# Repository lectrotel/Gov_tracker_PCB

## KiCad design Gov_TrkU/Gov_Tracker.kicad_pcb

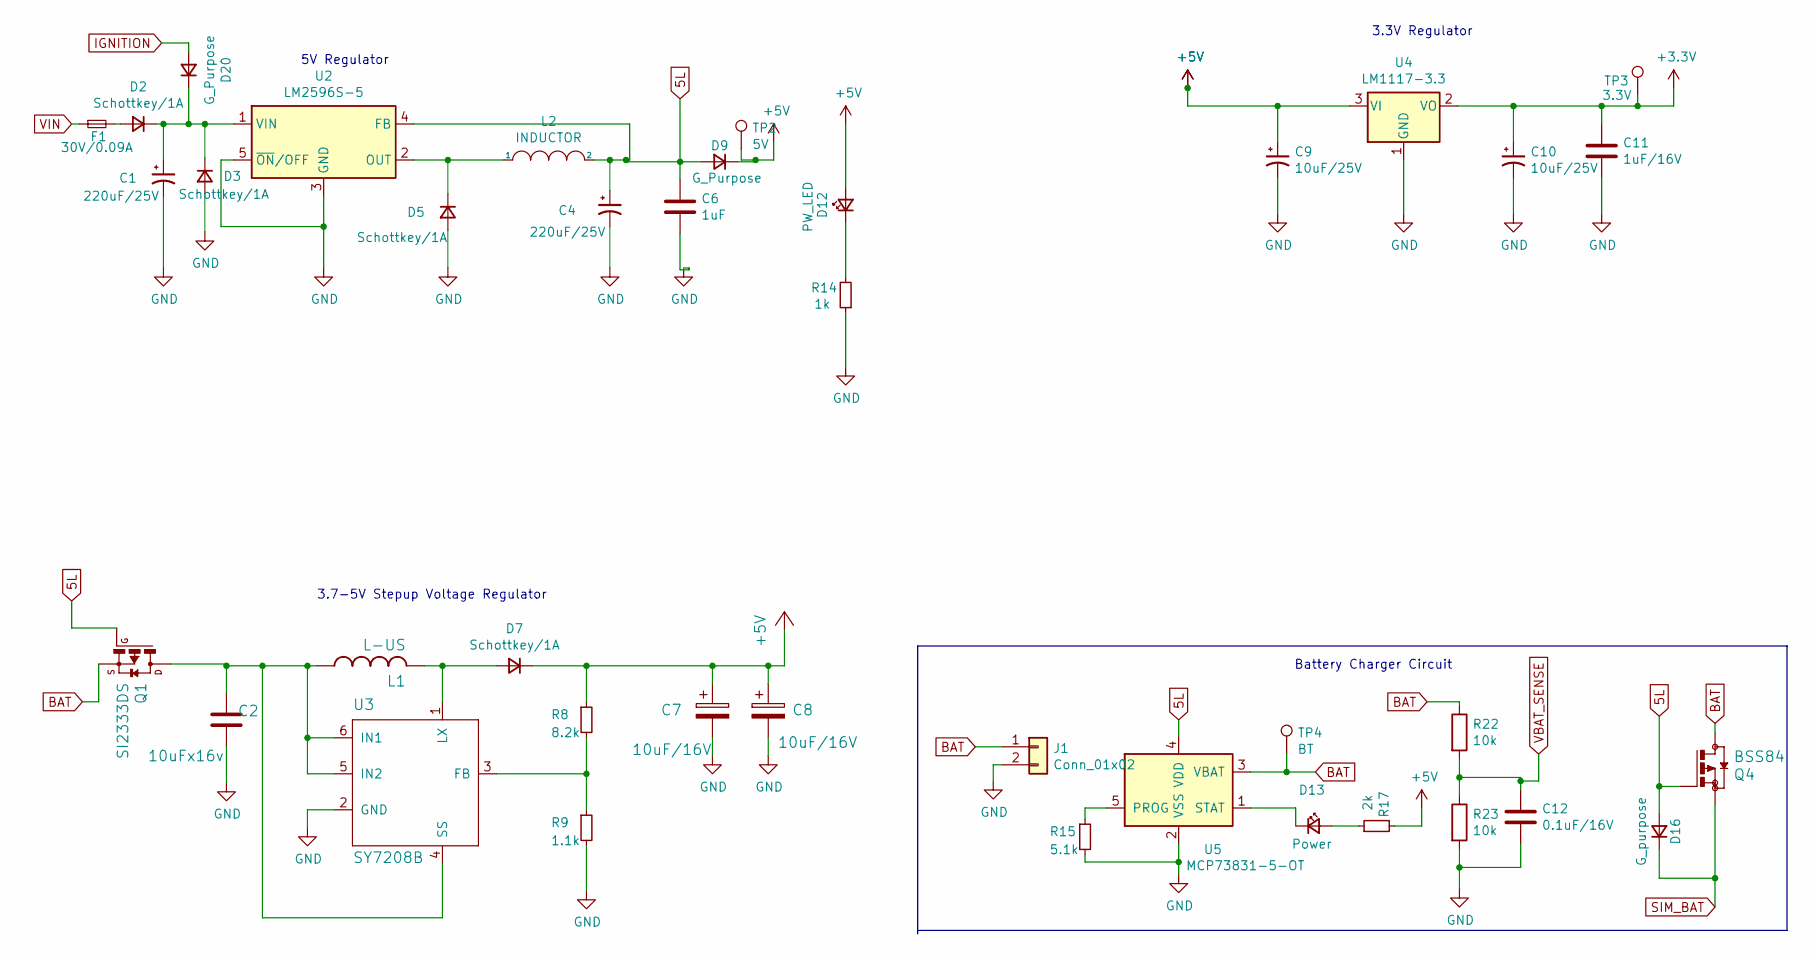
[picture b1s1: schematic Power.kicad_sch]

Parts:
C1, C4: 220uF/25V; CP_Elec_8x6.9
C2: 10uFx16v; C_0603_1608Metric
C6: 1uF; C_0603_1608Metric
C7, C8: 10uF/16V; C_0603_1608Metric
C9, C10: 10uF/25V; CP_Radial_D5.0mm_P2.50mm
C11: 1uF/16V; C_0603_1608Metric
C12: 0.1uF/16V; C_0603_1608Metric
D2, D3, D5, D7: Schottkey/1A; D_SMA
D9, D20: G_Purpose; D_SMA
D12: PW_LED; LED_0805_2012Metric
D13: Power; LED_0805_2012Metric
D16: G_purpose; D_SMA
F1: 30V/0.09A; Fuse_BelFuse_0ZRE0005FF_L8.3mm_W3.8mm
J1: Conn_01x02; JST_PH_B2B-PH-K_1x02_P2.00mm_Vertical
L1: L-US; L_Taiyo-Yuden_NR-60xx
L2: INDUCTOR; L_Pulse_PA4320
Q1: SI2333DS; SC-59
Q4: BSS84; SOT-23
R8: 8.2k; R_0603_1608Metric
R9: 1.1k; R_0603_1608Metric
R14: 1k; R_0603_1608Metric
R15: 5.1k; R_0603_1608Metric
R17: 2k; R_0603_1608Metric
R22, R23: 10k; R_0603_1608Metric
TP2: 5V; TestPoint_Pad_1.0x1.0mm
TP3: 3.3V; TestPoint_Pad_1.0x1.0mm
TP4: BT; TestPoint_Pad_1.0x1.0mm
U2: LM2596S-5; TO-263-5_TabPin3
U3: SY7208B; SOT-23-6
U4: LM1117-3.3; SOT-223-3_TabPin2
U5: MCP73831-5-OT; SOT-23-5

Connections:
5L: C4.1, C6.1, D9.2 (A), D16.2 (A), L2.2, Q1.1 (G), Q4.1 (G), U2.4 (FB), U5.4 (VDD); also elsewhere on the board
+5V: C7.1, C8.1, C9.1, D7.1 (K), D9.1 (K), D12.2 (A), R8.1, R17.2, TP2.1, U4.3 (VI); also elsewhere on the board
BAT: J1.1, Q1.2 (S), Q4.3 (D), R22.1, TP4.1, U5.3 (VBAT)
GND: C1.2, C2.2, C4.2, C6.2, C7.2, C8.2, C9.2, C10.2, C11.2, C12.2, D3.2 (A), D5.2 (A), J1.2, R9.2, R14.1, R15.2, R23.2, U2.3 (GND), U2.5 (~ON/OFF), U3.2 (GND), U4.1 (GND), U5.2 (VSS); also elsewhere on the board
IGNITION: D20.2 (A); also elsewhere on the board
unnamed: D2.2 (A), F1.2
unnamed: C1.1, D2.1 (K), D3.1 (K), D20.1 (K), U2.1 (VIN)
unnamed: D5.1 (K), L2.1, U2.2 (OUT)
unnamed: D7.2 (A), L1.2, U3.1 (LX)
unnamed: D12.1 (K), R14.2
unnamed: D13.2 (A), R17.1
unnamed: D13.1 (K), U5.1 (STAT)
unnamed: C2.1, L1.1, Q1.3 (D), U3.4 (SS), U3.5 (IN2), U3.6 (IN1)
unnamed: R8.2, R9.1, U3.3 (FB)
unnamed: R15.1, U5.5 (PROG)
SIM_BAT: D16.1 (K), Q4.2 (S); also elsewhere on the board
VBAT_SENSE: C12.1, R22.2, R23.1; also elsewhere on the board
VIN: F1.1; also elsewhere on the board

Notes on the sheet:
3.7-5V Stepup Voltage Regulator
Battery Charger Circuit
3.3V Regulator
5V Regulator

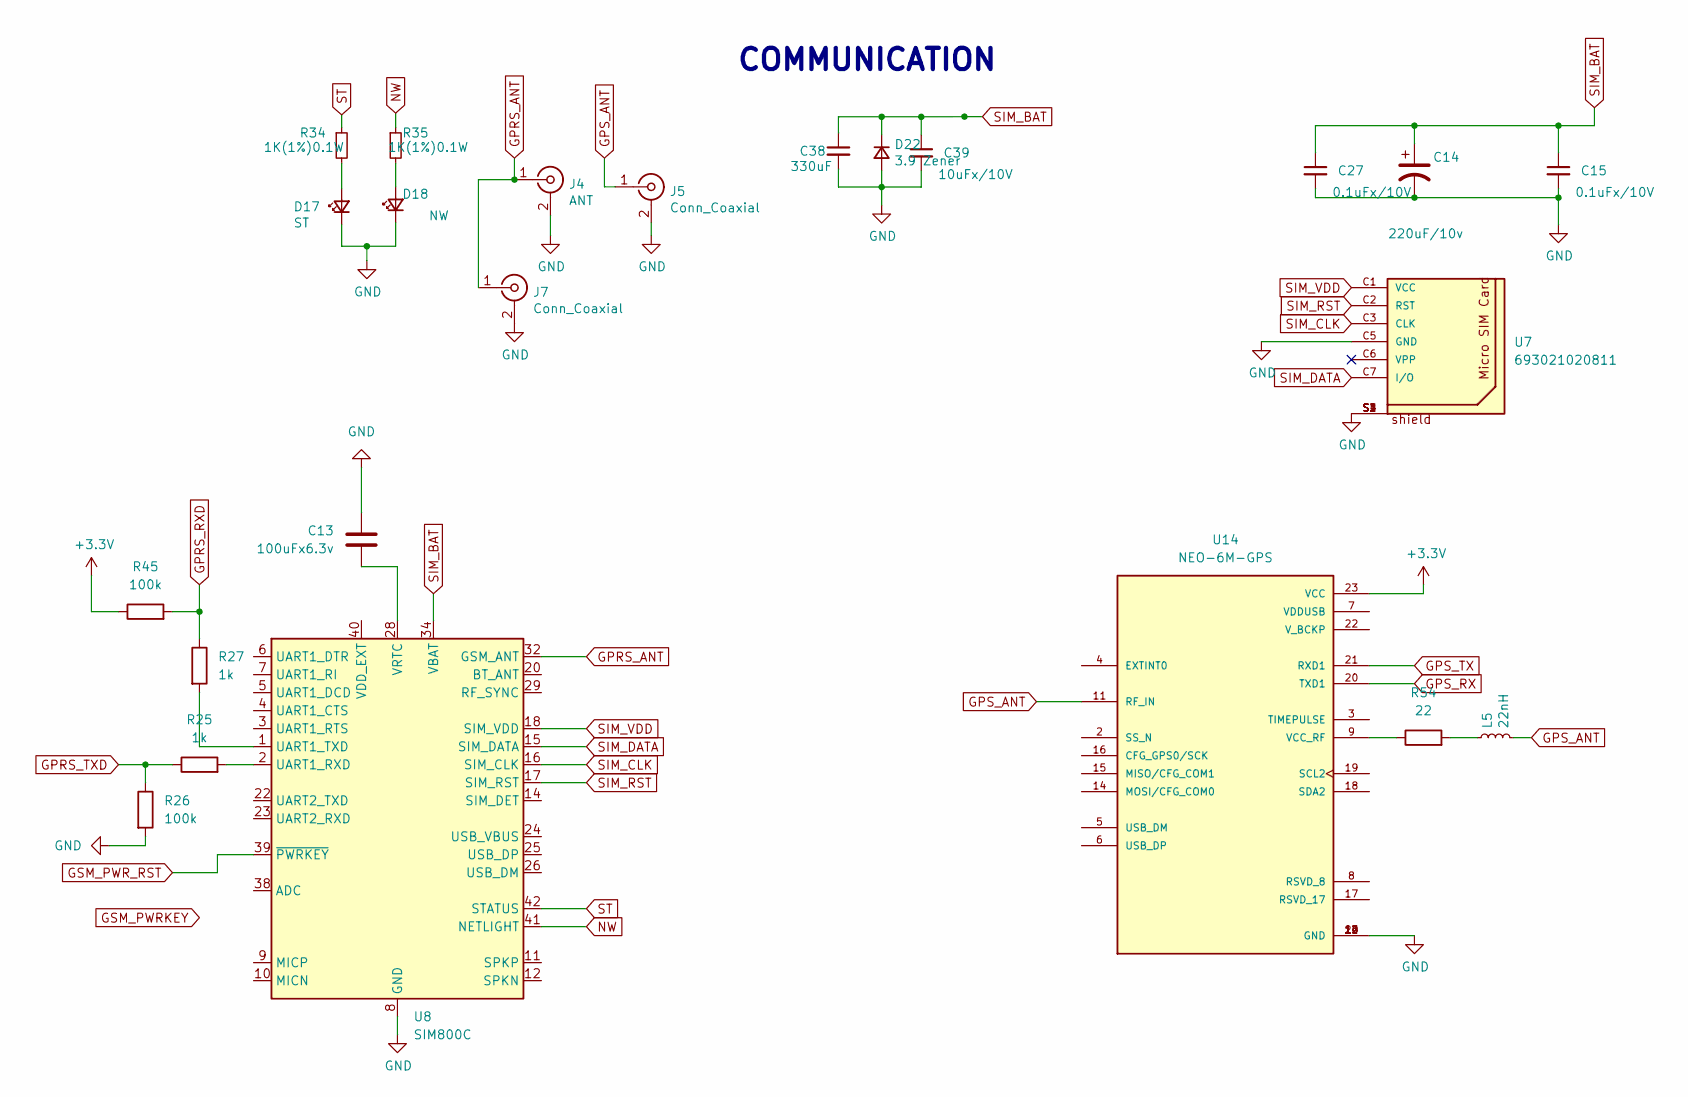
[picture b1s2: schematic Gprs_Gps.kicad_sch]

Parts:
C13: 100uFx6.3v; C_Elec_5x5.8
C14: 220uF/10v; CP_Elec_8x6.5
C15, C27: 0.1uFx/10V; C_0805_2012Metric
C38: 330uF; CP_EIA-6032-15_Kemet-U
C39: 10uFx/10V; C_0603_1608Metric
D17: ST; LED_0805_2012Metric
D18: NW; LED_0805_2012Metric
D22: 3.9 Zener; D_SOD-123
J4: ANT; SMA_Amphenol_132291_Vertical
J5: Conn_Coaxial; SMA_Amphenol_132291_Vertical
J7: Conn_Coaxial; U.FL_Molex_MCRF_73412-0110_Vertical
L5: 22nH; L_1206_3216Metric
R25, R27: 1k; R_0603_1608Metric
R26, R45: 100k; R_0603_1608Metric
R34, R35: 1K(1%)0.1W; R_0603_1608Metric
R54: 22; R_0603_1608Metric
U7: 693021020811; PART-NUMBER 693120035011
U8: SIM800C; SIMCom_SIM800C
U14: NEO-6M-GPS; XCVR_NEO-6M-GPS; PARTREV R15

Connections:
GND: C13.1, C14.2, C15.2, C27.2, C38.2, C39.2, D17.1 (K), D18.1 (K), D22.2 (A), J4.2 (Ext), J5.2 (Ext), J7.2 (Ext), R26.2, U7.C5 (GND), U7.S1, U7.S2, U7.S3, U7.S4, U8.8 (GND), U8.13 (GND), U8.19 (GND), U8.21 (GND), U8.27 (GND), U8.30 (GND), U8.31 (GND), U8.33 (GND), U8.36 (GND), U8.37 (GND), U14.10 (GND), U14.12 (GND), U14.13 (GND), U14.24 (GND); also elsewhere on the board
GPRS_ANT: J4.1 (In), J7.1 (In), U8.32 (GSM_ANT)
GPRS_RXD: R27.1, R45.2; also elsewhere on the board
GPRS_TXD: R25.1, R26.1; also elsewhere on the board
GPS_ANT: J5.1 (In), L5.2, U14.11 (RF_IN)
GPS_RX: U14.20 (TXD1); also elsewhere on the board
GPS_TX: U14.21 (RXD1); also elsewhere on the board
GSM_PWR_RST: U8.39 (~PWRKEY); also elsewhere on the board
NW: R35.1, U8.41 (NETLIGHT)
unnamed: D17.2 (A), R34.2
unnamed: D18.2 (A), R35.2
unnamed: L5.1, R54.2
unnamed: R25.2, U8.2 (UART1_RXD)
unnamed: R27.2, U8.1 (UART1_TXD)
unnamed: C13.2, U8.28 (VRTC)
unnamed: R54.1, U14.9 (VCC_RF)
SIM_BAT: C14.1, C15.1, C27.1, C38.1, C39.1, D22.1 (K), U8.34 (VBAT), U8.35 (VBAT); also elsewhere on the board
SIM_CLK: U7.C3 (CLK), U8.16 (SIM_CLK)
SIM_DATA: U7.C7 (I/O), U8.15 (SIM_DATA)
SIM_RST: U7.C2 (RST), U8.17 (SIM_RST)
SIM_VDD: U7.C1 (VCC), U8.18 (SIM_VDD)
ST: R34.1, U8.42 (STATUS)

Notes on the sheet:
COMMUNICATION

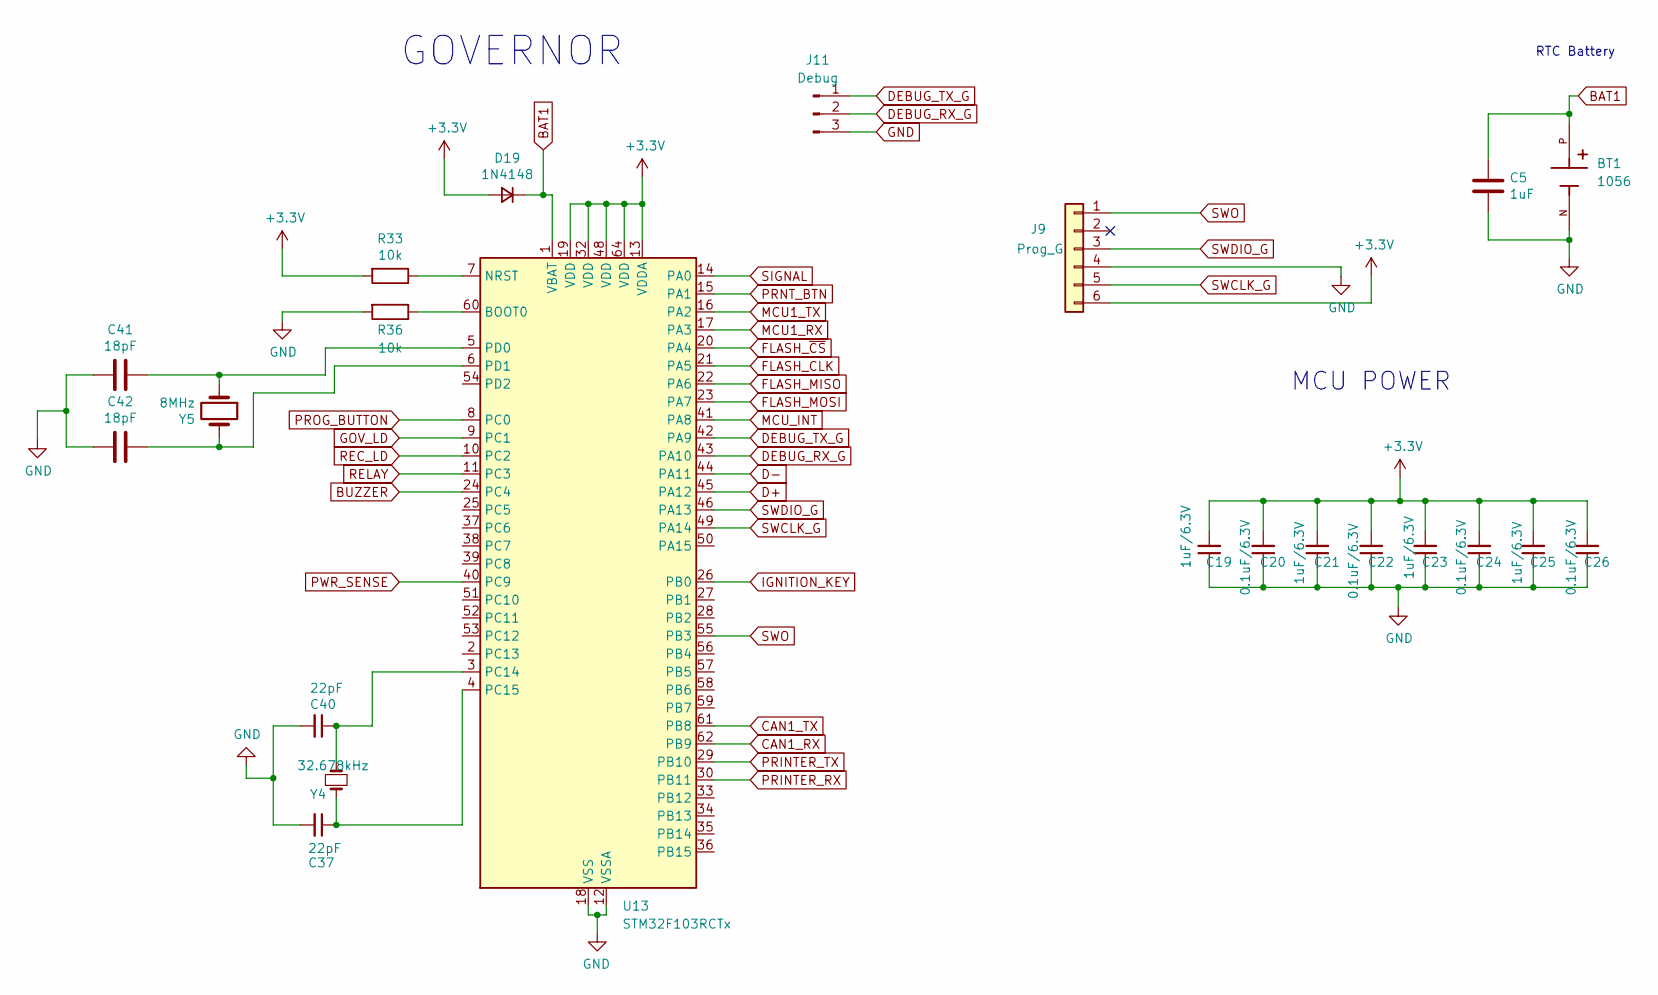
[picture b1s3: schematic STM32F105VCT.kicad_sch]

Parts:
BT1: 1056; BAT_1056; PARTREV D
C5: 1uF; C_0603_1608Metric
C19, C21, C23, C25: 1uF/6.3V; C_0603_1608Metric
C20, C22, C24, C26: 0.1uF/6.3V; C_0603_1608Metric
C37, C40: 22pF; C_0603_1608Metric
C41, C42: 18pF; C_0603_1608Metric
D19: 1N4148; D_SOD-123
J9: Prog_G; PinSocket_1x06_P2.54mm_Vertical
J11: Debug; PinHeader_1x03_P2.54mm_Vertical
R33, R36: 10k; R_0603_1608Metric
U13: STM32F103RCTx; LQFP-64_10x10mm_P0.5mm
Y4: 32.678kHz; Crystal_DS10_D1.0mm_L4.3mm_Vertical
Y5: 8MHz; Crystal_HC49-U_Vertical

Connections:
BAT1: BT1.P, C5.1, D19.1 (K), U13.1 (VBAT)
BUZZER: U13.24 (PC4); also elsewhere on the board
CAN1_RX: U13.62 (PB9)
CAN1_TX: U13.61 (PB8)
D+: U13.45 (PA12); also elsewhere on the board
D-: U13.44 (PA11); also elsewhere on the board
DEBUG_RX_G: J11.2, U13.43 (PA10)
DEBUG_TX_G: J11.1, U13.42 (PA9)
FLASH_CLK: U13.21 (PA5); also elsewhere on the board
FLASH_MISO: U13.22 (PA6); also elsewhere on the board
FLASH_MOSI: U13.23 (PA7); also elsewhere on the board
FLASH_~CS: U13.20 (PA4); also elsewhere on the board
GND: BT1.N, C5.2, C19.1, C20.1, C21.1, C22.1, C23.1, C24.1, C25.1, C26.1, C37.2, C40.2, C41.1, C42.1, J9.4, J11.3, R36.2, U13.12 (VSSA), U13.18 (VSS), U13.31 (VSS), U13.47 (VSS), U13.63 (VSS); also elsewhere on the board
GOV_LD: U13.9 (PC1); also elsewhere on the board
IGNITION_KEY: U13.26 (PB0); also elsewhere on the board
MCU1_RX: U13.17 (PA3); also elsewhere on the board
MCU1_TX: U13.16 (PA2); also elsewhere on the board
MCU_INT: U13.41 (PA8); also elsewhere on the board
unnamed: R36.1, U13.60 (BOOT0)
unnamed: R33.1, U13.7 (NRST)
unnamed: C40.1, U13.3 (PC14), Y4.2
unnamed: C37.1, U13.4 (PC15), Y4.1
unnamed: C41.2, U13.5 (PD0), Y5.1
unnamed: C42.2, U13.6 (PD1), Y5.2
PRINTER_RX: U13.30 (PB11); also elsewhere on the board
PRINTER_TX: U13.29 (PB10); also elsewhere on the board
PRNT_BTN: U13.15 (PA1); also elsewhere on the board
PROG_BUTTON: U13.8 (PC0); also elsewhere on the board
PWR_SENSE: U13.40 (PC9); also elsewhere on the board
REC_LD: U13.10 (PC2); also elsewhere on the board
RELAY: U13.11 (PC3); also elsewhere on the board
SIGNAL: U13.14 (PA0); also elsewhere on the board
SWCLK_G: J9.5, U13.49 (PA14)
SWDIO_G: J9.3, U13.46 (PA13)
SWO: J9.1, U13.55 (PB3)

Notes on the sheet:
MCU POWER
RTC Battery
GOVERNOR

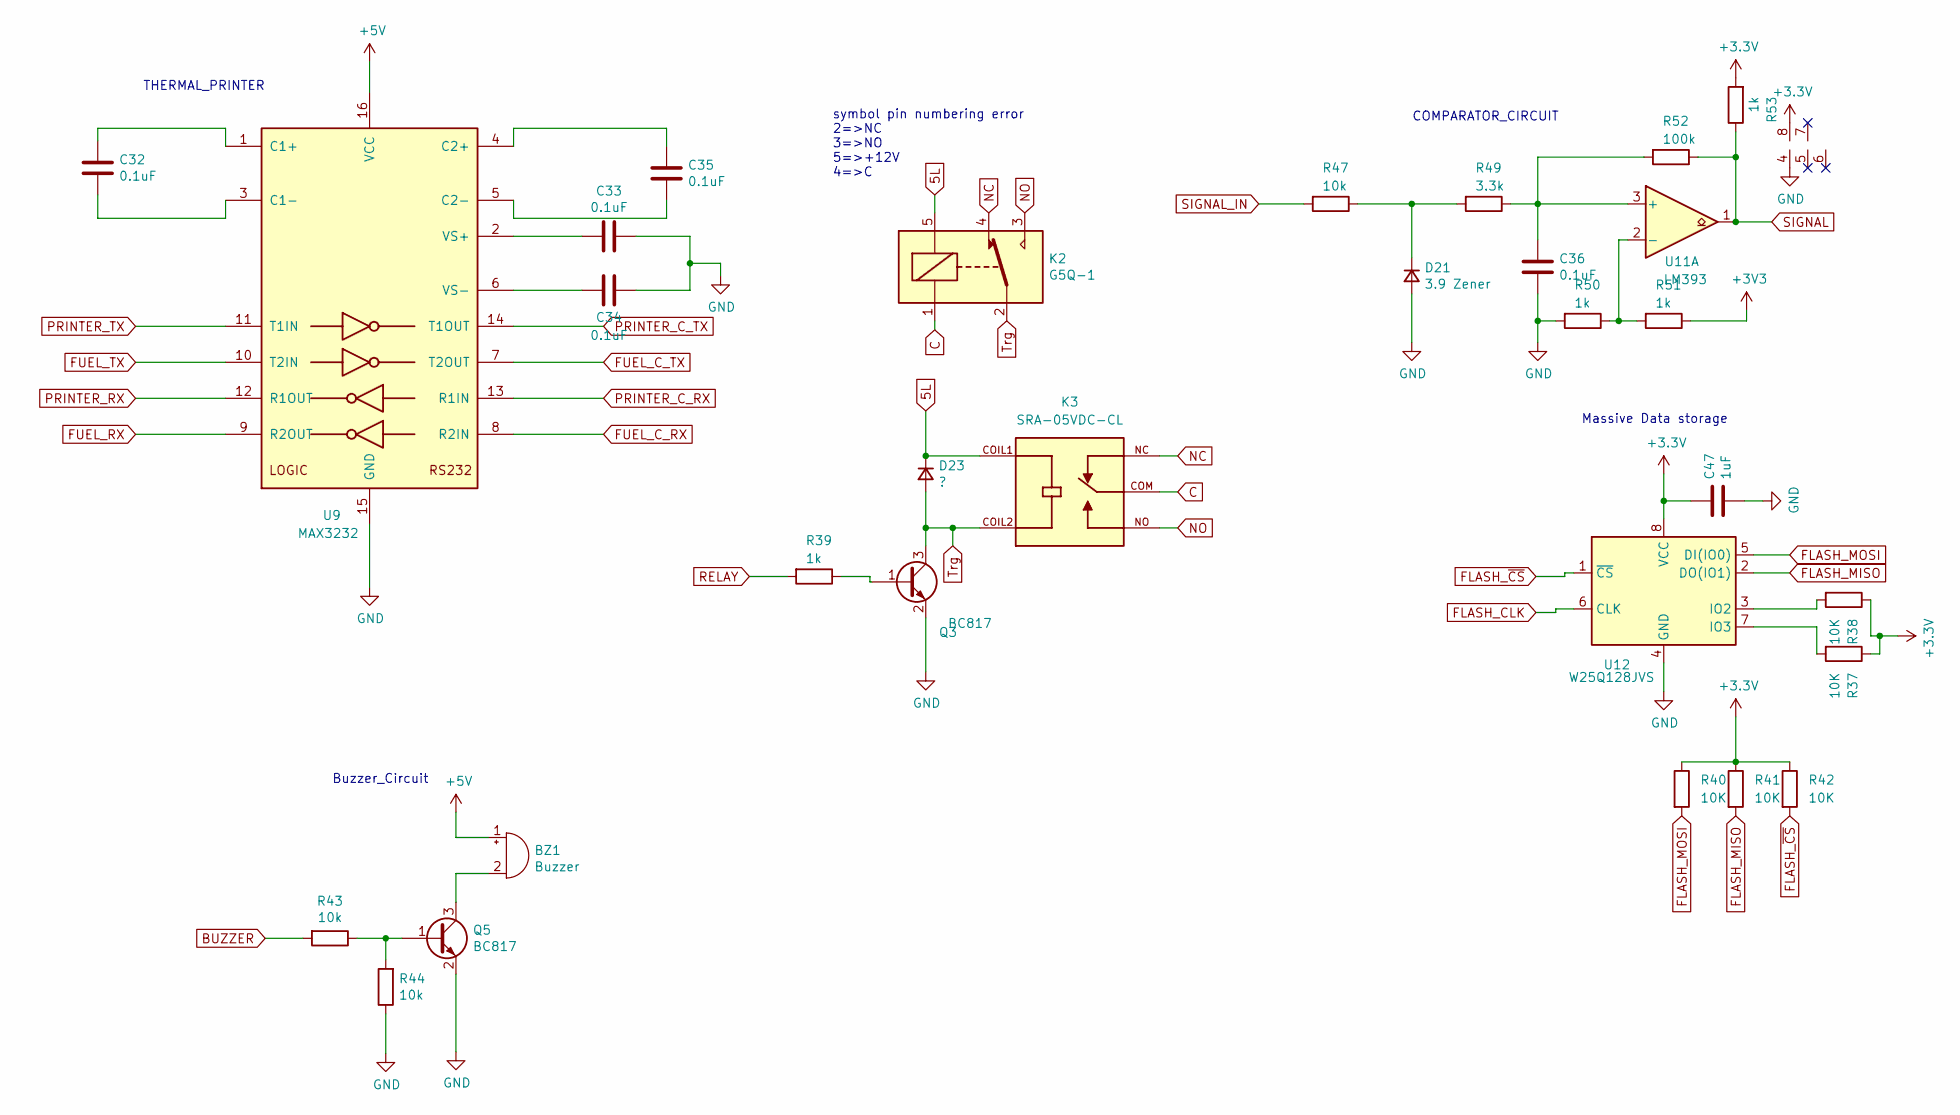
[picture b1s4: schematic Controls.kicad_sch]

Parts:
BZ1: Buzzer; MagneticBuzzer_ProSignal_ABI-009-RC
C32, C33, C34, C35, C36: 0.1uF; C_0603_1608Metric
C47: 1uF; C_0603_1608Metric
D21: 3.9 Zener; D_SOD-123
D23: ?; D_SMA
K2: G5Q-1; Relay_SPDT_Omron-G5LE-1
K3: SRA-05VDC-CL; RELAY_SRA-05VDC-CL; PARTREV NA
Q3, Q5: BC817; SOT-23
R37, R38, R40, R41, R42: 10K; R_0603_1608Metric
R39, R50, R51, R53: 1k; R_0603_1608Metric
R43, R44, R47: 10k; R_0603_1608Metric
R49: 3.3k; R_0603_1608Metric
R52: 100k; R_0603_1608Metric
U9: MAX3232; SOP65P640X110-16N
U11: LM393; SO08
U12: W25Q128JVS; SOIC-8_5.23x5.23mm_P1.27mm

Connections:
5L: D23.1 (K), K2.5, K3.COIL1; also elsewhere on the board
+5V: BZ1.1 (-), U9.16 (VCC); also elsewhere on the board
BUZZER: R43.2; also elsewhere on the board
C: K2.1, K3.COM; also elsewhere on the board
FLASH_CLK: U12.6 (CLK); also elsewhere on the board
FLASH_MISO: R41.2, U12.2 (DO(IO1)); also elsewhere on the board
FLASH_MOSI: R40.2, U12.5 (DI(IO0)); also elsewhere on the board
FLASH_~CS: R42.2, U12.1 (~CS); also elsewhere on the board
FUEL_C_RX: U9.8 (R2IN); also elsewhere on the board
FUEL_C_TX: U9.7 (T2OUT); also elsewhere on the board
FUEL_RX: U9.9 (R2OUT); also elsewhere on the board
FUEL_TX: U9.10 (T2IN); also elsewhere on the board
GND: C33.1, C34.1, C36.2, C47.2, D21.2 (A), Q3.2 (E), Q5.2 (E), R44.1, R50.2, U9.15 (GND), U11.4, U12.4 (GND); also elsewhere on the board
NC: K2.4, K3.NC; also elsewhere on the board
NO: K2.3, K3.NO; also elsewhere on the board
unnamed: BZ1.2 (+), Q5.3 (C)
unnamed: D21.1 (K), R47.1, R49.2
unnamed: Q3.1 (B), R39.1
unnamed: Q5.1 (B), R43.1, R44.2
unnamed: C32.1, U9.1 (C1+)
unnamed: C32.2, U9.3 (C1-)
unnamed: C35.1, U9.4 (C2+)
unnamed: C35.2, U9.5 (C2-)
unnamed: C33.2, U9.2 (VS+)
unnamed: C34.2, U9.6 (VS-)
unnamed: C36.1, R49.1, R52.2, U11.3 (+)
unnamed: R50.1, R51.2, U11.2 (-)
unnamed: R38.2, U12.3 (IO2)
unnamed: R37.2, U12.7 (IO3)
PRINTER_C_RX: U9.13 (R1IN); also elsewhere on the board
PRINTER_C_TX: U9.14 (T1OUT); also elsewhere on the board
PRINTER_RX: U9.12 (R1OUT); also elsewhere on the board
PRINTER_TX: U9.11 (T1IN); also elsewhere on the board
RELAY: R39.2; also elsewhere on the board
SIGNAL: R52.1, R53.1, U11.1; also elsewhere on the board
SIGNAL_IN: R47.2; also elsewhere on the board
Trg: D23.2 (A), K2.2, K3.COIL2, Q3.3 (C)

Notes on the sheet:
THERMAL_PRINTER
COMPARATOR_CIRCUIT
Massive Data storage
Buzzer_Circuit
symbol pin numbering error 2=>NC 3=>NO 5=>+12V 4=>C

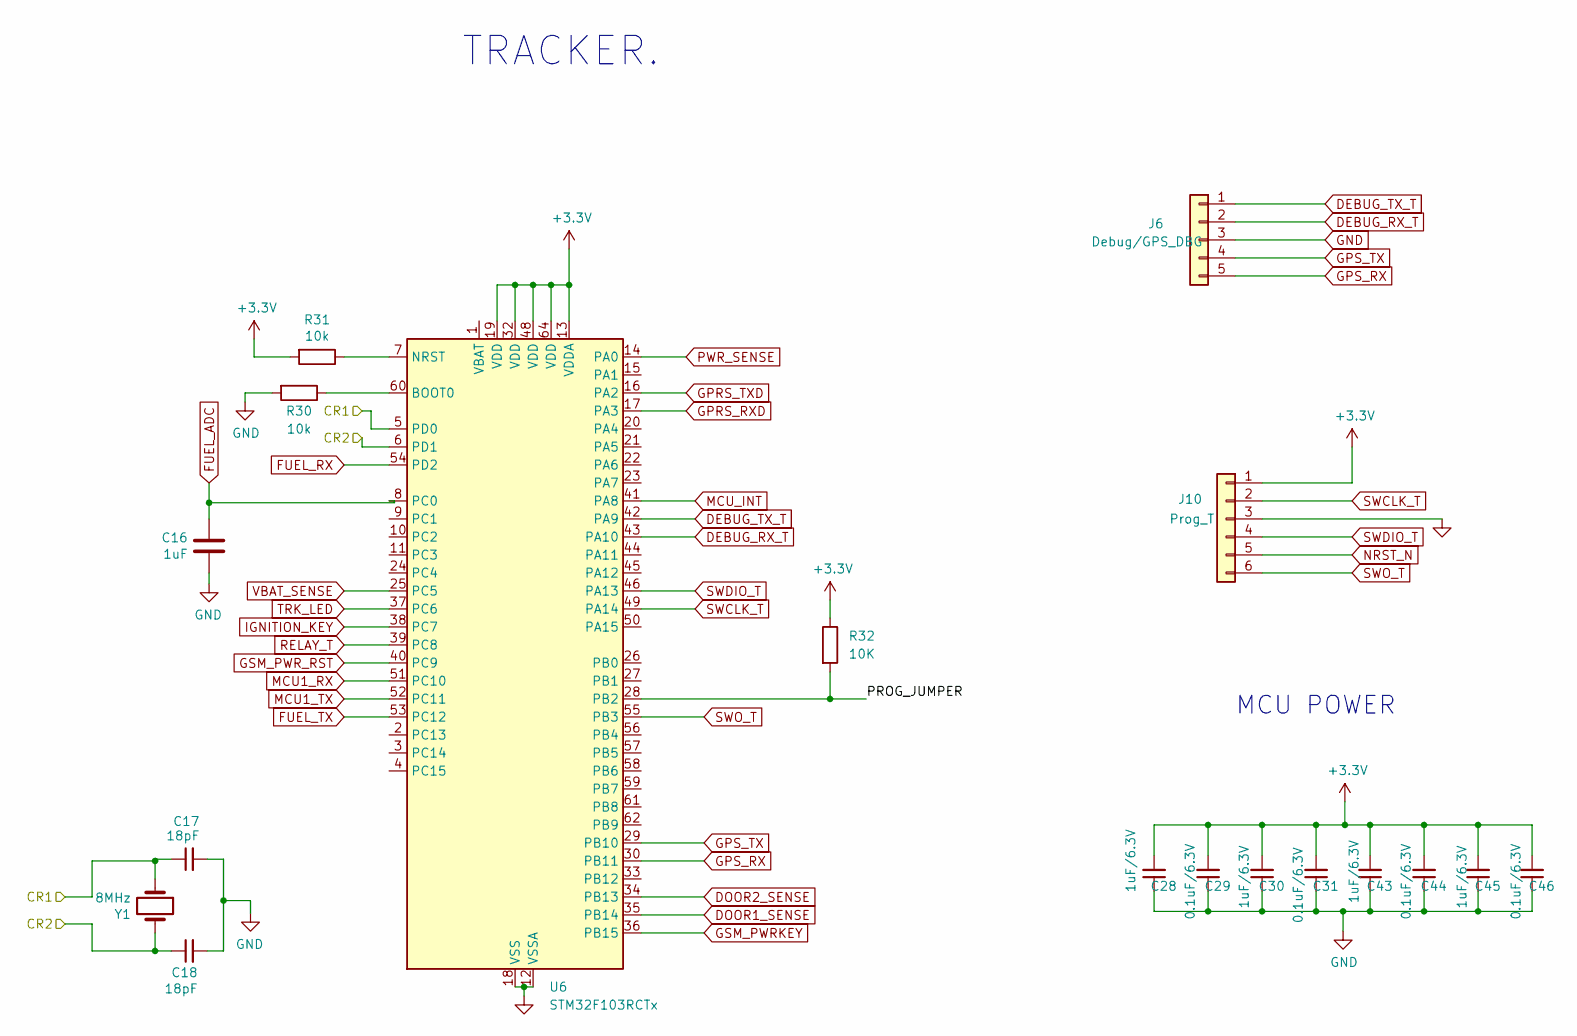
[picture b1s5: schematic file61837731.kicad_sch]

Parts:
C16: 1uF; C_0603_1608Metric
C17, C18: 18pF; C_0603_1608Metric
C28, C30, C43, C45: 1uF/6.3V; C_0603_1608Metric
C29, C31, C44, C46: 0.1uF/6.3V; C_0603_1608Metric
J6: Debug/GPS_DBG; PinSocket_1x05_P2.54mm_Vertical
J10: Prog_T; PinSocket_1x06_P2.54mm_Vertical
R30, R31: 10k; R_0603_1608Metric
R32: 10K; R_0603_1608Metric
U6: STM32F103RCTx; LQFP-64_10x10mm_P0.5mm
Y1: 8MHz; Crystal_HC49-U_Vertical

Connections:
/TRACKER/CR1: C17.1, U6.5 (PD0), Y1.1
/TRACKER/CR2: C18.1, U6.6 (PD1), Y1.2
/TRACKER/PROG_JUMPER: R32.2, U6.28 (PB2)
DEBUG_RX_T: J6.2, U6.43 (PA10)
DEBUG_TX_T: J6.1, U6.42 (PA9)
DOOR1_SENSE: U6.35 (PB14); also elsewhere on the board
DOOR2_SENSE: U6.34 (PB13); also elsewhere on the board
FUEL_ADC: C16.1, U6.8 (PC0); also elsewhere on the board
FUEL_RX: U6.54 (PD2); also elsewhere on the board
FUEL_TX: U6.53 (PC12); also elsewhere on the board
GND: C16.2, C17.2, C18.2, C28.1, C29.1, C30.1, C31.1, C43.1, C44.1, C45.1, C46.1, J6.3, J10.3, R30.2, U6.12 (VSSA), U6.18 (VSS), U6.31 (VSS), U6.47 (VSS), U6.63 (VSS); also elsewhere on the board
GPRS_RXD: U6.17 (PA3); also elsewhere on the board
GPRS_TXD: U6.16 (PA2); also elsewhere on the board
GPS_RX: J6.5, U6.30 (PB11); also elsewhere on the board
GPS_TX: J6.4, U6.29 (PB10); also elsewhere on the board
GSM_PWRKEY: U6.36 (PB15)
GSM_PWR_RST: U6.40 (PC9); also elsewhere on the board
IGNITION_KEY: U6.38 (PC7); also elsewhere on the board
MCU1_RX: U6.51 (PC10); also elsewhere on the board
MCU1_TX: U6.52 (PC11); also elsewhere on the board
MCU_INT: U6.41 (PA8); also elsewhere on the board
NRST_N: J10.5
unnamed: R30.1, U6.60 (BOOT0)
unnamed: R31.1, U6.7 (NRST)
PWR_SENSE: U6.14 (PA0); also elsewhere on the board
RELAY_T: U6.39 (PC8); also elsewhere on the board
SWCLK_T: J10.2, U6.49 (PA14)
SWDIO_T: J10.4, U6.46 (PA13)
SWO_T: J10.6, U6.55 (PB3)
TRK_LED: U6.37 (PC6); also elsewhere on the board
VBAT_SENSE: U6.25 (PC5); also elsewhere on the board

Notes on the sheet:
TRACKER.
MCU POWER

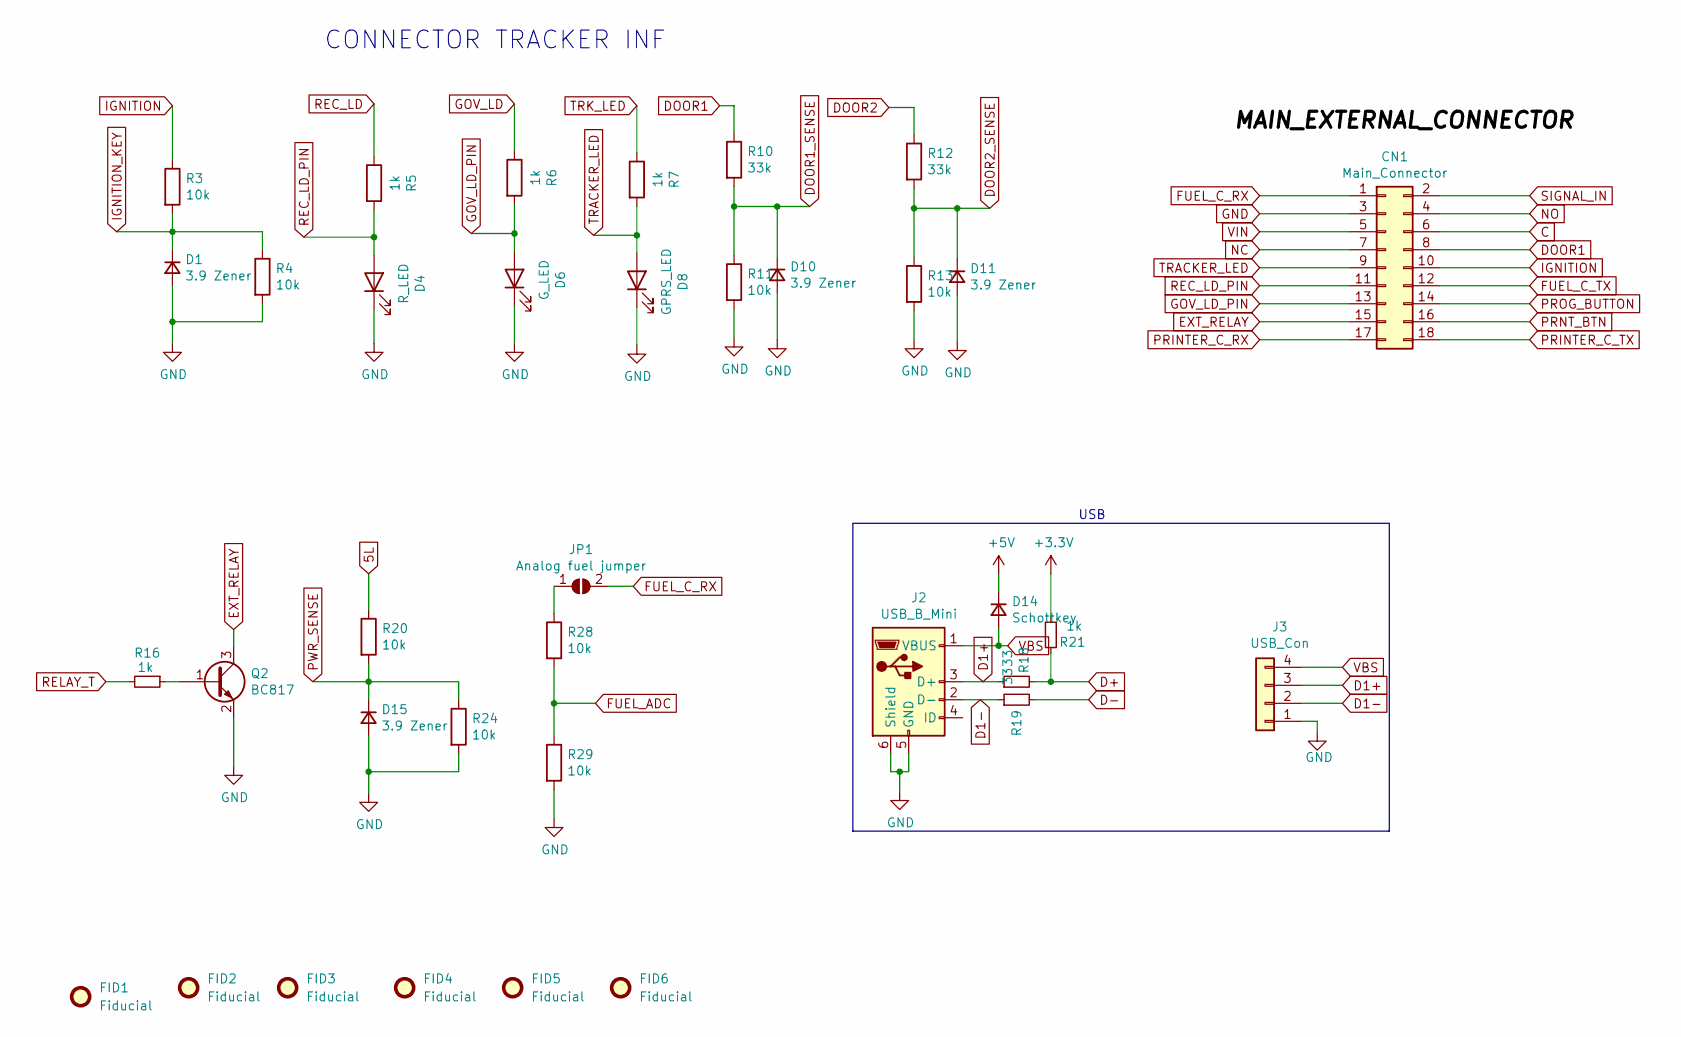
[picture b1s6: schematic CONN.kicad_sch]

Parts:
CN1: Main_Connector; 66201821122
D1, D10, D11, D15: 3.9 Zener; D_SOD-123
D4: R_LED; LED_0805_2012Metric
D6: G_LED; LED_0805_2012Metric
D8: GPRS_LED; LED_0805_2012Metric
D14: Schottkey; D_SOD-123
FID1, FID2, FID3: Fiducial; Fiducial_1mm_Mask3mm
FID4: Fiducial; Fiducial_1.5mm_Mask3mm
FID5, FID6: Fiducial; Fiducial_0.75mm_Mask1.5mm
J2: USB_B_Mini; USB_Mini-B_Lumberg_2486_01_Horizontal
J3: USB_Con; PinSocket_1x04_P2.54mm_Vertical
JP1: Analog fuel jumper; SolderJumper-2_P1.3mm_Open_RoundedPad1.0x1.5mm
Q2: BC817; SOT-23
R3, R4, R11, R13, R20, R24, R28, R29: 10k; R_0603_1608Metric
R5, R6, R7, R16, R21: 1k; R_0603_1608Metric
R10, R12: 33k; R_0603_1608Metric
R18, R19: 33; R_0603_1608Metric

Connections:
5L: R20.1; also elsewhere on the board
+5V: D14.1 (K); also elsewhere on the board
C: CN1.6; also elsewhere on the board
D1+: J2.3 (D+), J3.3, R18.1
D1-: J2.2 (D-), J3.2, R19.1
D+: R18.2, R21.2; also elsewhere on the board
D-: R19.2; also elsewhere on the board
DOOR1: CN1.8, R10.1
DOOR1_SENSE: D10.1 (K), R10.2, R11.1; also elsewhere on the board
DOOR2: R12.1
DOOR2_SENSE: D11.1 (K), R12.2, R13.1; also elsewhere on the board
EXT_RELAY: CN1.15, Q2.3 (C)
FUEL_ADC: R28.2, R29.1; also elsewhere on the board
FUEL_C_RX: CN1.1, JP1.2 (B); also elsewhere on the board
FUEL_C_TX: CN1.12; also elsewhere on the board
GND: CN1.3, D1.2 (A), D4.1 (K), D6.1 (K), D8.1 (K), D10.2 (A), D11.2 (A), D15.2 (A), J2.5 (GND), J2.6 (Shield), J3.1, Q2.2 (E), R4.2, R11.2, R13.2, R24.2, R29.2; also elsewhere on the board
GOV_LD: R6.1; also elsewhere on the board
GOV_LD_PIN: CN1.13, D6.2 (A), R6.2
IGNITION: CN1.10, R3.1; also elsewhere on the board
IGNITION_KEY: D1.1 (K), R3.2, R4.1; also elsewhere on the board
NC: CN1.7; also elsewhere on the board
NO: CN1.4; also elsewhere on the board
unnamed: JP1.1 (A), R28.1
unnamed: Q2.1 (B), R16.1
PRINTER_C_RX: CN1.17; also elsewhere on the board
PRINTER_C_TX: CN1.18; also elsewhere on the board
PRNT_BTN: CN1.16; also elsewhere on the board
PROG_BUTTON: CN1.14; also elsewhere on the board
PWR_SENSE: D15.1 (K), R20.2, R24.1; also elsewhere on the board
REC_LD: R5.1; also elsewhere on the board
REC_LD_PIN: CN1.11, D4.2 (A), R5.2
RELAY_T: R16.2; also elsewhere on the board
SIGNAL_IN: CN1.2; also elsewhere on the board
TRACKER_LED: CN1.9, D8.2 (A), R7.2
TRK_LED: R7.1; also elsewhere on the board
VBS: D14.2 (A), J2.1 (VBUS), J3.4
VIN: CN1.5; also elsewhere on the board

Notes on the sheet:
USB
CONNECTOR TRACKER INF

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
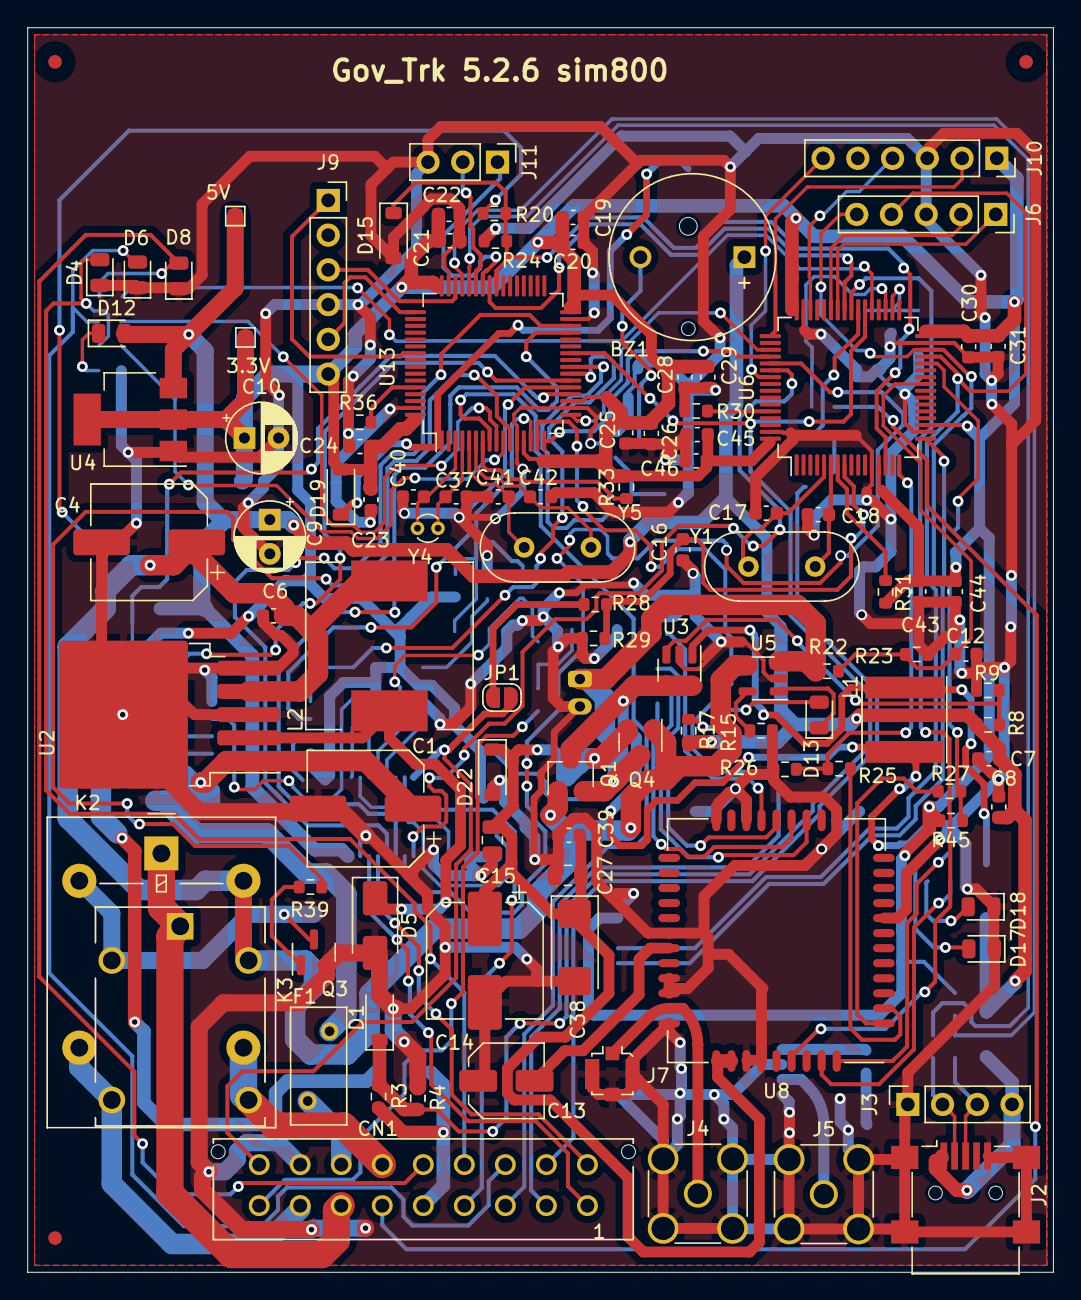
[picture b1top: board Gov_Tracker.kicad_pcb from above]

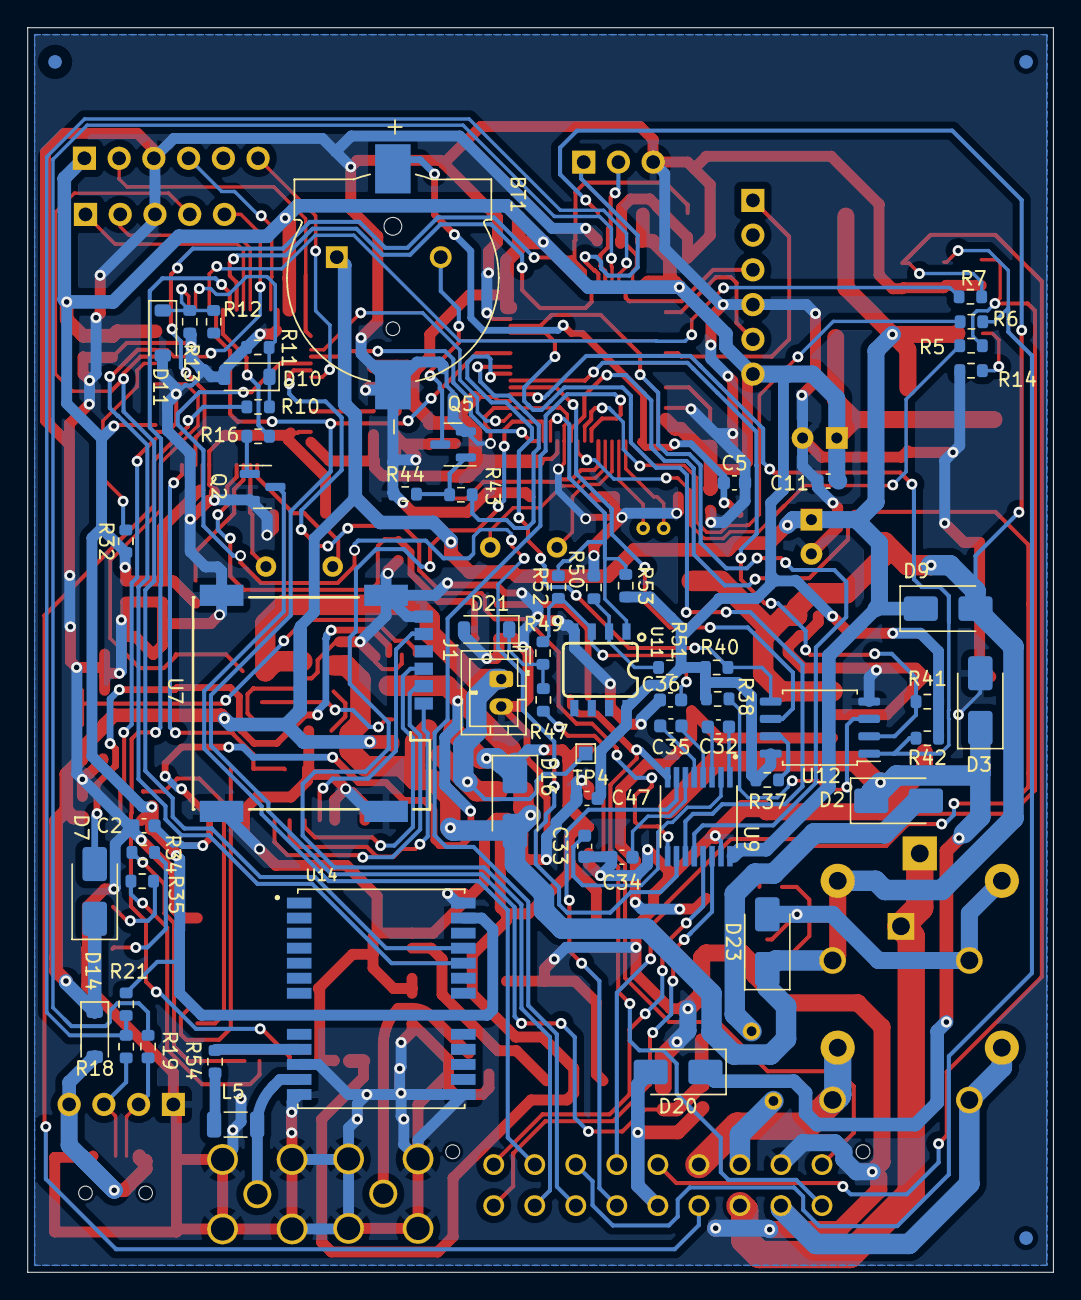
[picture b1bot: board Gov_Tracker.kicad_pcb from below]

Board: 2 copper layers, 75.0 x 91.0 mm, 168 parts (63 on the bottom side), 121 nets.

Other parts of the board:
3.3V: 3.3V; TestPoint_Pad_1.0x1.0mm
5V: 5V; TestPoint_Pad_1.0x1.0mm

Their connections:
+5V: 5V.1; also elsewhere on the board

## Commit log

2025-01-13 First design iteration
2025-01-14 panelised board
2025-01-14 Made amendments
2025-01-14 saved
2025-01-15 Panel almost complete
2025-02-19 final design
2025-02-28 antenae swap
2025-03-06 updated the pannel and generated gerber files
2025-03-06 updated the diode positioning
2025-03-07 added garber
2025-03-07 5.2.6 final edit
2025-03-28 PCB files
